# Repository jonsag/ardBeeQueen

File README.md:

# ardBeeQueen
A simple project to control a bee queen breeding chamber

Parts needed
===============
1 x Arduino Pro Mini, kjell.com art#87964  
1 x Arduino USB to Serial Converter, kjell.com art#87872  
2 x Arduino Single Relay Module, kjell.com art#87878  
1 x LCD Display, kjell.com art#90215  
1 x Dallas 1-wire Temp and Humidity Sensor DHT11, kjell.com art#87877 or  
1 x Dallas 1-wire Temp and Humidity Sensor DHT22, kjell.com art#90647  
1 x Rotary encoder, kjell.com art#87918  
1 x 10kohm Potentiometer, kjell.com art#90633  
1 x 220ohm resistor  
1 x 10K ohm resistor  
2 x 0,47uF capacitor  

Casing to hold everything

Wires and soldering material  

If you want to build a PCB using the Gerber file you will also need some headers and connnectors.  

Building electrical  
===============
Use schemes ardBeeQueenFritz* or Schematic_ardBeeQueen-v2_ardBeeQueen-v2_* to build.  
If you do not use the encoder you must still pull up D7 with a 10K resistor to VCC.  

Eagle PCB  
===============
If using the 50x52 PCB in Documents/Eagle directory, you can mount it in box electrokit.com, art#12109003  
Outside measures: 69 x 102 x 37 mm  
Inside measures: 63 x 96 x 33 mm  

If using the 105x84 PCB in Documents/Eagle directory, you can mount it in box electrokit.com, art#12109005  
Outside measures: 103 x 148 x 56 mm  
Insode measures: 96 x 142 x 52 mm  

Note
===============
All commands in the following instructions are run on Linux  
All links are valid and versions are the latest as of february 2019  

Set up Arduino IDE
===============
Go to https://www.arduino.cc/en/main/software and download Arduino IDE for your architecture and system  
>$ wget https://downloads.arduino.cc/arduino-1.8.10-linux64.tar.xz  
>$ tar xvJf arduino-1.8.10-linux64.tar.xz -C ~/bin/  
>$ ln -s arduino-1.8.10/arduino ~/bin/arduino  

Get libraries 
---------------

Adafruit Unified Sensor library  
---------------
Download library from https://www.arduinolibraries.info/libraries/adafruit-unified-sensor  
>$ wget http://downloads.arduino.cc/libraries/github.com/adafruit/Adafruit_Unified_Sensor-1.0.3.zip  
>$ unzip Adafruit_Unified_Sensor-1.0.3.zip -d ~/bin/arduino-1.8.10/libraries/  
>$ mv ~/bin/arduino-1.8.10/libraries/Adafruit_Unified_Sensor-1.0.3 ~/bin/arduino-1.8.10/libraries/Adafruit_Unified_Sensor  

DHT sensor library  
---------------
Download library from https://www.arduinolibraries.info/libraries/dht-sensor-library  
>$ wget http://downloads.arduino.cc/libraries/github.com/adafruit/DHT_sensor_library-1.3.7.zip  
>$ unzip DHT_sensor_library-1.3.7.zip -d ~/bin/arduino-1.8.10/libraries/  
>$ mv ~/bin/arduino-1.8.10/libraries/DHT_sensor_library-1.3.7 ~/bin/arduino-1.8.10/libraries/DHT_sensor_library  

Programming the Arduino Mini Pro
===============

If using the Arduino USB 2 Serial  
--------------------
Connect the programmer to your Pro Mini  
GND/BLK -> GND  
+5V -> VCC  
TX -> RX  
RX -> TX  
EXT RESET -> GRN

Open your sketch in Arduino IDE  
Select 'Tools'->'Port'  
* /dev/ttyACM0 or  
* /dev/ttyUSB0  

Select 'Tools'->'Board'  
For the 3.3V versions of the Arduino Pro Mini, select:  
* Arduino Pro or  
* Pro Mini (3.3V, 8 MHz) w/ ATmega328P or  
* Arduino Pro or  
* Pro Mini (3.3V, 8 MHz) w/ ATmega168  
(depending on the microcontroller on your board)  
For the 5V versions of the Arduino Pro Mini, select  
* Arduino Duemilanove or  
* Nano w/ ATmega328P or  
* Arduino Diecimila, Duemilanove (this is what I used) or  
* Nano w/ ATmega168

If using the PC-PL2303 Cable  
---------------
Black cable -> GND  
Green cable -> TXD  
White cable -> RXD  
Red cable -> VCC (5V)  

You will have to press the reset button on the arduino to reset it right before the upload from Arduino IDE.  

Fritzing  
===============
Download fritzing at http://fritzing.org/download/  

>$ wget http://fritzing.org/download/0.9.3b/linux-64bit/fritzing-0.9.3b.linux.AMD64.tar.bz2  
>$ tar jxvf ~/Downloads/fritzing-0.9.3b.linux.AMD64.tar.bz2 -C ~/bin/  
>$ ln -s fritzing-0.9.3b.linux.AMD64/Fritzing ~/bin/fritzing  

EasyEDA  
==============
Use easyEDA online at https://easyeda.com/editor or download client from https://easyeda.com/page/download  

>$ wget https://image.easyeda.com/files/easyeda-client-linux-x64.zip  
>$ unzip easyeda-client-linux-x64.zip  
>$ cd easyeda-client-linux-x64  
>$ sudo bash install.sh  

Download local router from https://docs.easyeda.com/en/PCB/Route/index.html#Local-Auto-Router  
>$ wget https://image.easyeda.com/files/EasyEDA-Router-v0.8.1.zip  
>$ unzip EasyEDA-Router-v0.8.1.zip  
>$ cd EasyEDA-Router-v0.8.1  

Start router with  
>$ bash lin64.sh  

Autodesk EAGLE
===================
Download EAGLE at https://www.autodesk.com/products/eagle/free-download  

>$ tar xvzf Autodesk_EAGLE_9.3.1_English_Linux_64bit.tar.gz -C ~/bin  
>$ ln -s eagle-9.3.1/eagle ~/bin/eagle  

Start and sign in with your Autodesk account

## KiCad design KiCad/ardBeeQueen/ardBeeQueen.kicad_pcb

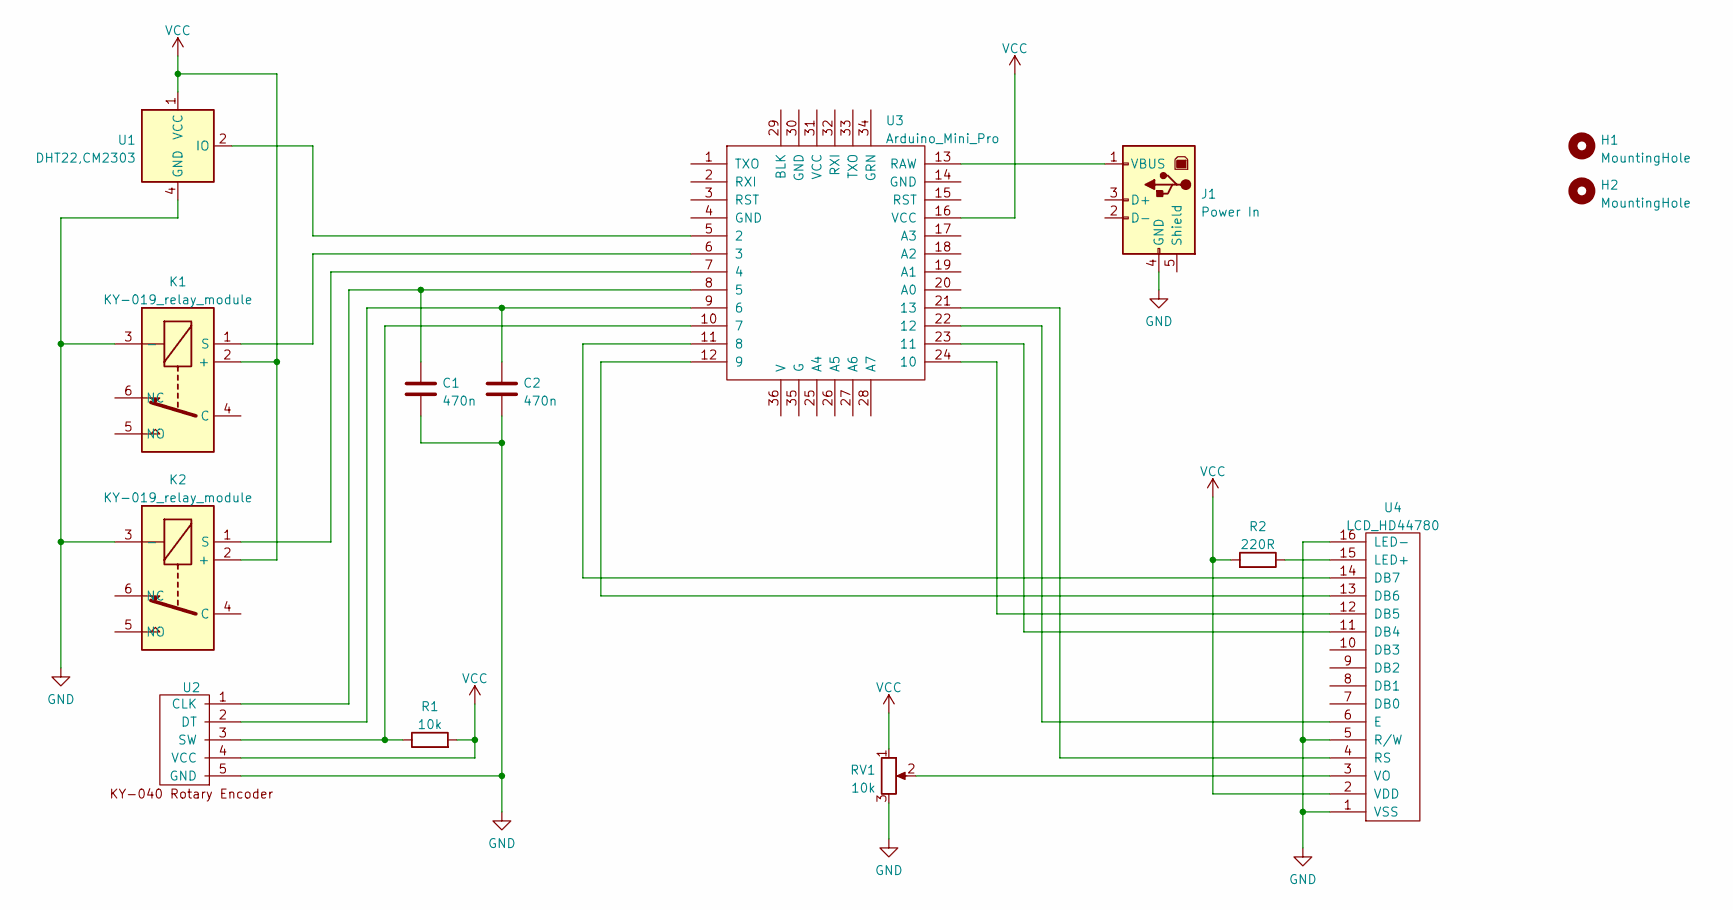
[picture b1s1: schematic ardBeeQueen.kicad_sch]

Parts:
C1, C2: 470n; C_Disc_D3.0mm_W1.6mm_P2.50mm_larg
H1, H2: MountingHole; MountingHole_3.2mm_M3
J1: Power In; USB_B_OST_USB-B1HSxx_Horizontal_large
K1, K2: KY-019_relay_module; 3-pin JST KY-019 relay
R1: 10k; R_Axial_DIN0207_L6.3mm_D2.5mm_P10.16mm_Horizontal_larger_pa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
R2: 220R; R_Axial_DIN0207_L6.3mm_D2.5mm_P10.16mm_Horizontal_larger_pa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
RV1: 10k; Potentiometer_Bourns_3339P_Vertical_large
U1: DHT22,CM2303; 3-pin JST DHT11, DHT22
U2: KY-040_Rotary_Encoder; 5-pin JST Rotary Encoder
U3: Arduino_Mini_Pro; Arduino_Pro_Mini_vC_only_sides_larger_pads
U4: LCD_HD44780; LCD_HD44780_16x2_w_headers_no outlinelarge

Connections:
GND: C1.2, C2.2, J1.4 (GND), K1.3 (-), K2.3 (-), RV1.3, U1.4 (GND), U2.5 (GND), U4.1 (VSS), U4.5 (R/W), U4.16 (LED-)
unnamed: C1.1, U2.1 (CLK), U3.8 (5)
unnamed: C2.1, U2.2 (DT), U3.9 (6)
unnamed: J1.1 (VBUS), U3.13 (RAW)
unnamed: K1.1 (S), U3.6 (3)
unnamed: K2.1 (S), U3.7 (4)
unnamed: R1.1, U2.3 (SW), U3.10 (7)
unnamed: R2.1, U4.15 (LED+)
unnamed: RV1.2, U4.3 (VO)
unnamed: U1.2 (IO), U3.5 (2)
unnamed: U3.11 (8), U4.14 (DB7)
unnamed: U3.12 (9), U4.13 (DB6)
unnamed: U3.21 (13), U4.4 (RS)
unnamed: U3.22 (12), U4.6 (E)
unnamed: U3.23 (11), U4.11 (DB4)
unnamed: U3.24 (10), U4.12 (DB5)
VCC: K1.2 (+), K2.2 (+), R1.2, R2.2, RV1.1, U1.1 (VCC), U2.4 (VCC), U3.16 (VCC), U4.2 (VDD)

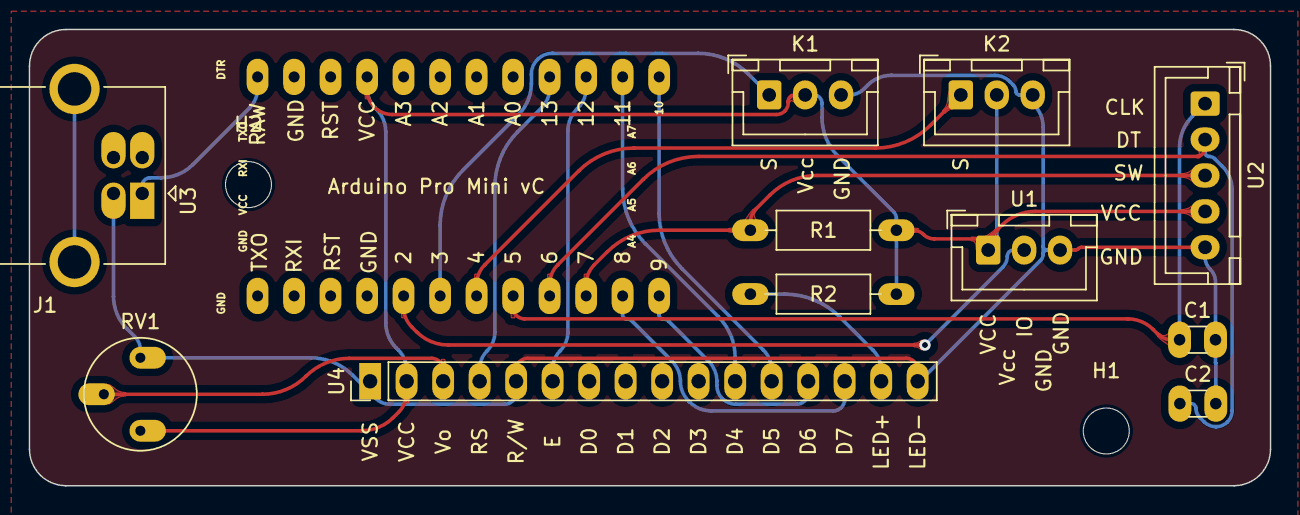
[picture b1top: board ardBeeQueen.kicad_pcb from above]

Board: 2 copper layers, 86.4 x 31.7 mm, 14 parts (0 on the bottom side), 17 nets.

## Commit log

2018-05-15 Added fritz image
2018-05-16 Now has a DHT11. Measures humidity abd temperature, has LCD, has both heating and cooling relay.
2019-02-21 Reorganizing
2019-02-21 Changed to new DHT library
2019-02-23 Updated fritz and sketch
2019-02-24 Haf to add another sketch, as my Arduino Mini Pro is broken. D2 and D3 are shorted to each other, and D10 is not usable.
2019-02-24 Added rotary encoder to sketch
2019-02-24 Some renaming
2019-02-25 Added rotary encoder for changing set point
2019-02-25 Updated fritz with new components
2019-02-26 Near completion- Also added schematics and PCB
2019-02-26 Minor fixes
2019-02-26 Added to part list
2019-03-04 Documents
2019-03-04 delete
2019-03-05 Added board with mounted relays.# WARNING: head commit changed in the meantime
    delete
2019-03-10 updated eagle docs
2019-10-06 updated ino
2019-10-07 deleted files from Eagle
2019-10-11 added PID sketch
2019-10-12 added another PID ino
2019-10-12 PID output to LCD
2019-10-12 added plotting function and new ino
2019-10-12 improved plotting
2019-10-12 outputs windowTime and onTimeVal
2019-10-12 comments and some cleanup
2019-10-12 added eagle schematics and PCBs
2019-10-13 bug in PID3
2019-10-17 updated LCD config
2019-10-19 added air circulation fan
2019-10-19 redid the LCD outout, some more comments
2019-10-19 starting on autotune version
2019-10-19 renames
2019-10-19 mostly serial output changes
2019-10-20 comments and output changes
2019-10-20 straightening
2019-10-20 bugs
2019-10-20 shape ups
2019-10-20 many ...
2019-10-20 added PID4, mostly beautifying(!)
2019-10-20 deleted dew points and heat index from PIID3
2020-01-25 Eagle update
2021-01-26 schematic image
2022-05-29 moved to kicad
2025-01-26 new kicad version
